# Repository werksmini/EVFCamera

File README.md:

# EVFCamera

A compact rangefinder-style digital camera built on a Raspberry Pi Zero 2 W and the Raspberry Pi HQ camera, with C/CS-mount lenses. You compose, review and change settings entirely through a 0.4" 1280×960 micro-OLED eye-level EVF.

## Hardware

| Part | Choice |
| --- | --- |
| Computer | Raspberry Pi Zero 2 W (hostname `EVFPi`) |
| Sensor | Raspberry Pi HQ camera (Sony IMX477) |
| Viewfinder | 0.4" 1280×960 HDMI micro-OLED, 12.5× eyepiece |
| Lenses | Fujinon-TV 9 mm f/1.4, 17 mm f/1.7 (C-mount) |
| Shutter | Alps SKRNPEE010 two-stage switch (bench: 6×6 tact switch) |
| Power | Adafruit bq25185 USB-C charger + 5 V boost, 1-cell Li-ion |
| Sensors | Deferred: MAX17048 fuel gauge, VCNL4040 eye sensor (I²C pins kept free) |

## Repository layout

| Folder | Contents |
| --- | --- |
| `bench/` | Standalone test scripts used while bringing up the hardware |
| `hardware/kicad/` | Footprints and PCB files |
| `docs/` | Roadmap and design notes |

| `evfcam/` | The camera app |
| `tests/` | Mode and control tests (run anywhere with the fake camera) |
| `tools/` | Helpers, e.g. `render_screens.py` draws every screen to PNG |

See [docs/roadmap.md](docs/roadmap.md) for the architecture and milestones.

## Setup on the Pi

Raspberry Pi OS Lite (64-bit), then:

```bash
sudo apt update && sudo apt full-upgrade -y
sudo raspi-config nonint do_i2c 0
sudo apt install -y python3-picamera2 --no-install-recommends
sudo apt install -y rpicam-apps-lite python3-pil python3-evdev python3-numpy python3-gpiozero i2c-tools git

mkdir -p ~/evfpi && cd ~/evfpi
python3 -m venv --system-site-packages .venv
source .venv/bin/activate
# later, for the deferred sensors:
# pip install adafruit-blinka adafruit-circuitpython-max1704x adafruit-circuitpython-vcnl4040
git clone https://github.com/werksmini/EVFCamera.git
```

Bench monitor (Waveshare 10.4" 1600×720, mounted upside down): add to the single line in `/boot/firmware/cmdline.txt`, then reboot:

```text
video=HDMI-A-1:1600x720,rotate=180
```

For the EVF instead: `video=HDMI-A-1:1280x960@60D`.

## Running the camera app

```bash
cd ~/evfpi/EVFCamera && git pull
python3 -m evfcam            # bench monitor (flipped, 960x720 window)
python3 -m evfcam --evf      # 0.4" EVF, 1280x960, not flipped
python3 -m evfcam --fake     # no camera: work on the UI anywhere
```

At the shutter press the screen goes dark with a white border and a red dot until the photo is saved, then live view returns with "SAVED". Review after the shot and the flash itself are in Menu > Display. In Shoot mode, the EV readout turns red with "MAX" when the exposure can't get any brighter.

Controls, typed in the SSH terminal or on a keyboard plugged into the Pi:

| Key | Camera control | Shoot | Magnify | Menu (page list) | Menu (inside a page) | Playback |
| --- | --- | --- | --- | --- | --- | --- |
| Space | Shutter (full) | Take photo | Take photo | Close | Close | Close |
| `h` | Shutter (half) | – | Close | Close | Close | Close |
| Enter | OK | Magnify 5× | 10×, then off | Open page | Step value / run action | – |
| ↑ ↓ | D-pad | ISO (Manual) | – | Move | Move | – |
| ← → | D-pad | – | – | ← close, → open | Change value | Browse |
| `m` | Menu | Open menu | Close | Close | Close menu | Close |
| `p` | Play | Playback | Playback | – | – | Close |
| `b` / Backspace | Back | Reset EV | Close | Close | Up to page list | Close |
| `[` `]` | Thumb wheel | EV (A) / shutter (S, M) | – | – | Change value | Browse |
| `q` | – | Quit | Quit | Quit | Quit | Quit |

Settings are saved to `~/.config/evfcam/settings.json` and come back after a restart.

The bench shutter button on GPIO 27 also works. Photos save to `~/evfpi/photos`.

Run the tests: `python3 tests/test_modes.py`

## Bench scripts

| Script | What it does |
| --- | --- |
| `bench/preview.py` | Live preview only |
| `bench/overlay.py` | Preview with exposure info and focus meter overlay |
| `bench/camera.py` | Overlay + shutter button on GPIO 27 (header pin 13, other leg to GND pin 14); saves full-res JPEGs to `~/evfpi/photos` |

```bash
cd ~/evfpi && source .venv/bin/activate
python3 EVFCamera/bench/camera.py
```

Set `FLIP = False` at the top of a script when using the EVF instead of the flipped bench monitor.

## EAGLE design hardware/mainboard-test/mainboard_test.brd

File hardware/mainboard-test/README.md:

# Test mainboard v0.1

First PCB for learning Fusion Electronics: connects the Pi Zero 2 W to the rear controls and to connectors for everything else. Placed but **not routed** — routing it in Fusion is the exercise.

| Ref | Part | Connects |
| --- | --- | --- |
| J1 | 2x20 header, 2.54 mm | Pi Zero 2 W (pin 1 lower-left; odd pins on the lower row, like the Pi seen from above) |
| SW1–SW5 | 6x6 mm through-hole tact switch | D-pad up, down, left, right, OK |
| SW6, SW7 | 6x6 mm tact switch | Back/Menu, Play |
| J2 | 1x2 header | 5 V in from the charger / PiSugar: 5V, GND |
| J3 | 1x3 header | Shutter (Alps SKRN): half, full, GND |
| J4 | 1x4 header | Thumb wheel: A, B, push, GND |
| J5 | 1x2 header | Front Fn button: FN, GND |
| J6 | 1x4 header | Top knob: A, B, push, GND |
| J7 | 1x5 header | I2C sensors (deferred): 3V3, GND, SDA, SCL, INT |

Nets and GPIOs: [netlist.csv](netlist.csv). They follow the project GPIO map; the thumb-wheel push uses GPIO 18.

**Switches are wired on diagonal pads (1 and 4)**, so they work whichever way round they're fitted.

**Milling-friendly:** single-sided, all through-hole, 1.8–2.0 mm pads on 1.0 mm holes, at least 1.5 mm copper between parts. Don't run traces between the 2.54 mm header pins (0.74 mm gap).

**Connecting the Pi:** easiest is a shrouded 2x20 box header for J1 and a 40-pin ribbon cable (like a T-Cobbler cable). If the Pi plugs straight onto this board instead, check which way up it sits first — a female header on the underside mirrors the pin order.

## Open in Fusion

1. Fusion: **File > Upload**, pick a project folder, select **both** `mainboard_test.sch` and `mainboard_test.brd`, Upload.
2. Leave **Create Electronics Design** ticked, OK.
3. Open the new Electronics Design; it holds the schematic and the PCB, linked.

## Regenerate

```bash
python3 make_mainboard.py   # writes .sch, .brd, netlist.csv
python3 preview.py          # writes mainboard_preview.png and prints the tightest spacing
```

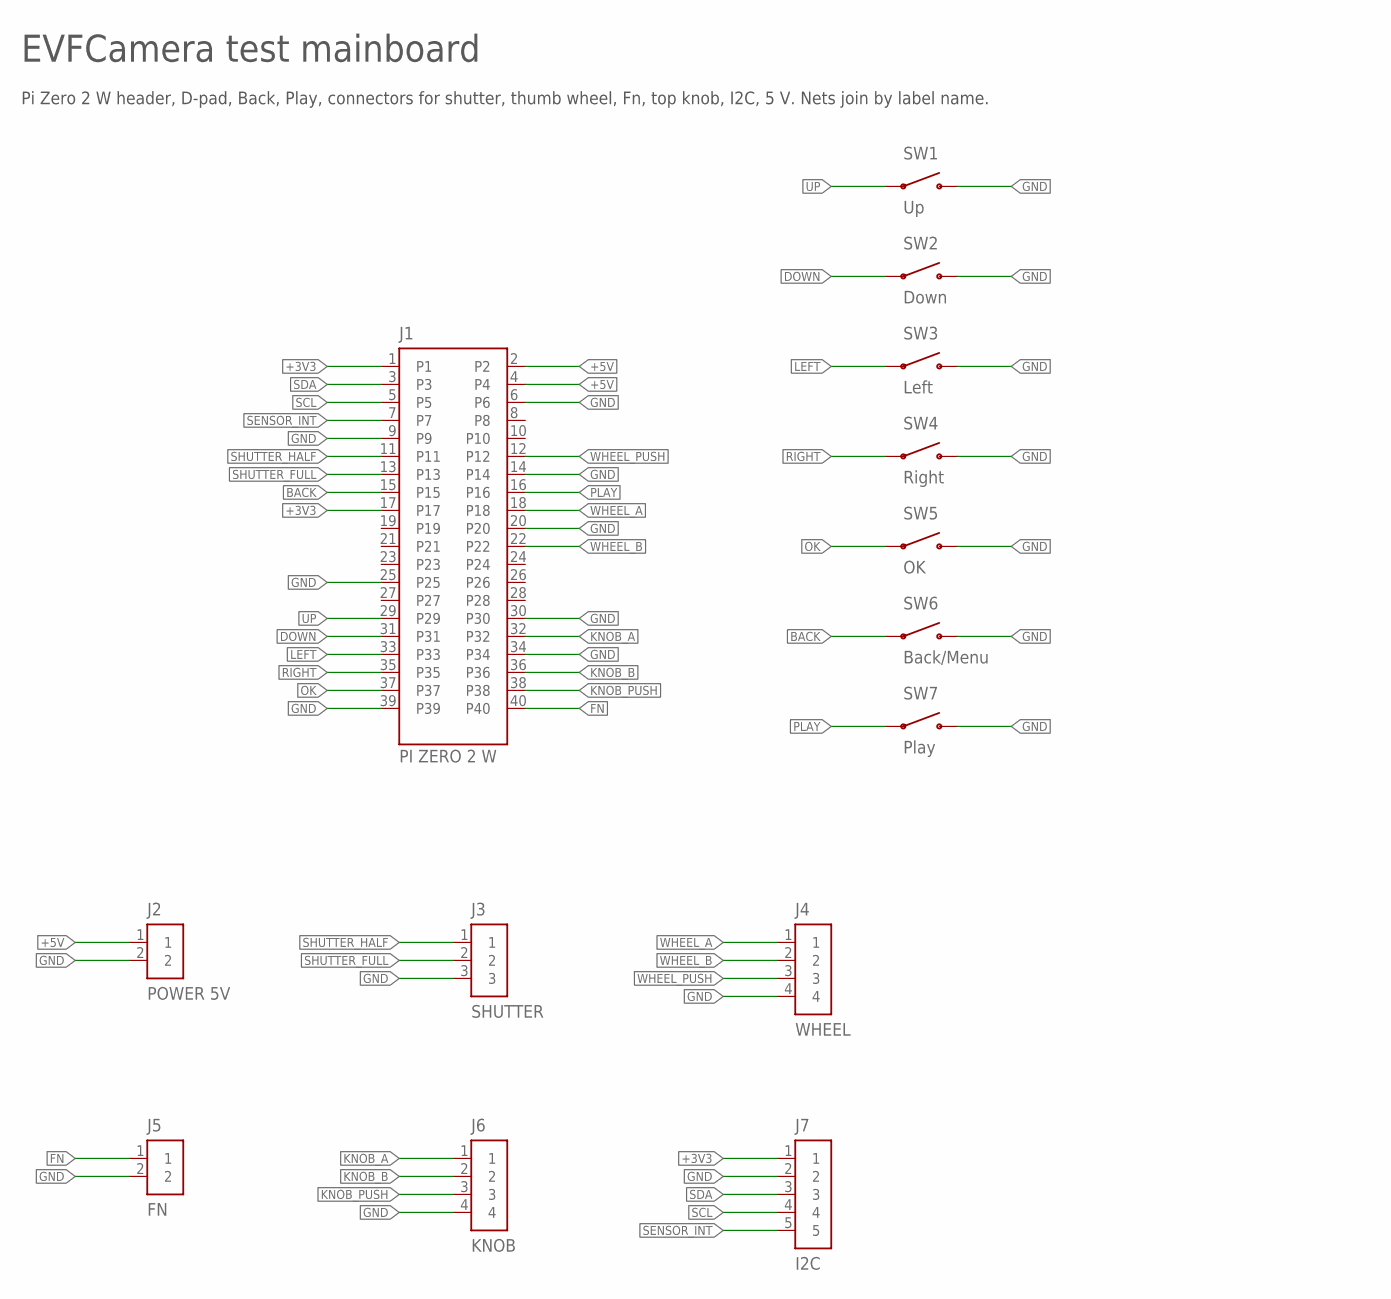
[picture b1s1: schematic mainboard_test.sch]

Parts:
J1: PI ZERO 2 W; PI_HEADER_2X20
J2: POWER 5V; HEADER_1X2
J3: SHUTTER; HEADER_1X3
J4: WHEEL; HEADER_1X4
J5: FN; HEADER_1X2
J6: KNOB; HEADER_1X4
J7: I2C; HEADER_1X5
SW1: Up; TACT_6X6_THT
SW2: Down; TACT_6X6_THT
SW3: Left; TACT_6X6_THT
SW4: Right; TACT_6X6_THT
SW5: OK; TACT_6X6_THT
SW6: Back/Menu; TACT_6X6_THT
SW7: Play; TACT_6X6_THT

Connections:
+3V3: J1.1, J1.17, J7.1
+5V: J1.2, J1.4, J2.1
BACK: J1.15, SW6.1 (A)
DOWN: J1.31, SW2.1 (A)
FN: J1.40, J5.1
GND: J1.6, J1.9, J1.14, J1.20, J1.25, J1.30, J1.34, J1.39, J2.2, J3.3, J4.4, J5.2, J6.4, J7.2, SW1.4 (B), SW2.4 (B), SW3.4 (B), SW4.4 (B), SW5.4 (B), SW6.4 (B), SW7.4 (B)
KNOB_A: J1.32, J6.1
KNOB_B: J1.36, J6.2
KNOB_PUSH: J1.38, J6.3
LEFT: J1.33, SW3.1 (A)
OK: J1.37, SW5.1 (A)
PLAY: J1.16, SW7.1 (A)
RIGHT: J1.35, SW4.1 (A)
SCL: J1.5, J7.4
SDA: J1.3, J7.3
SENSOR_INT: J1.7, J7.5
SHUTTER_FULL: J1.13, J3.2
SHUTTER_HALF: J1.11, J3.1
UP: J1.29, SW1.1 (A)
WHEEL_A: J1.18, J4.1
WHEEL_B: J1.22, J4.2
WHEEL_PUSH: J1.12, J4.3

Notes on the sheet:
EVFCamera test mainboard
Pi Zero 2 W header, D-pad, Back, Play, connectors for shutter, thumb wheel, Fn, top knob, I2C, 5 V. Nets join by label name.

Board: 1 copper layer, 14 parts (0 on the bottom side), 22 nets, no tracks yet.
